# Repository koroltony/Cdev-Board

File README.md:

# C-DEV-Board

Documentation of CDEV board. PCB for breadboard-type development. USB/Battery powered

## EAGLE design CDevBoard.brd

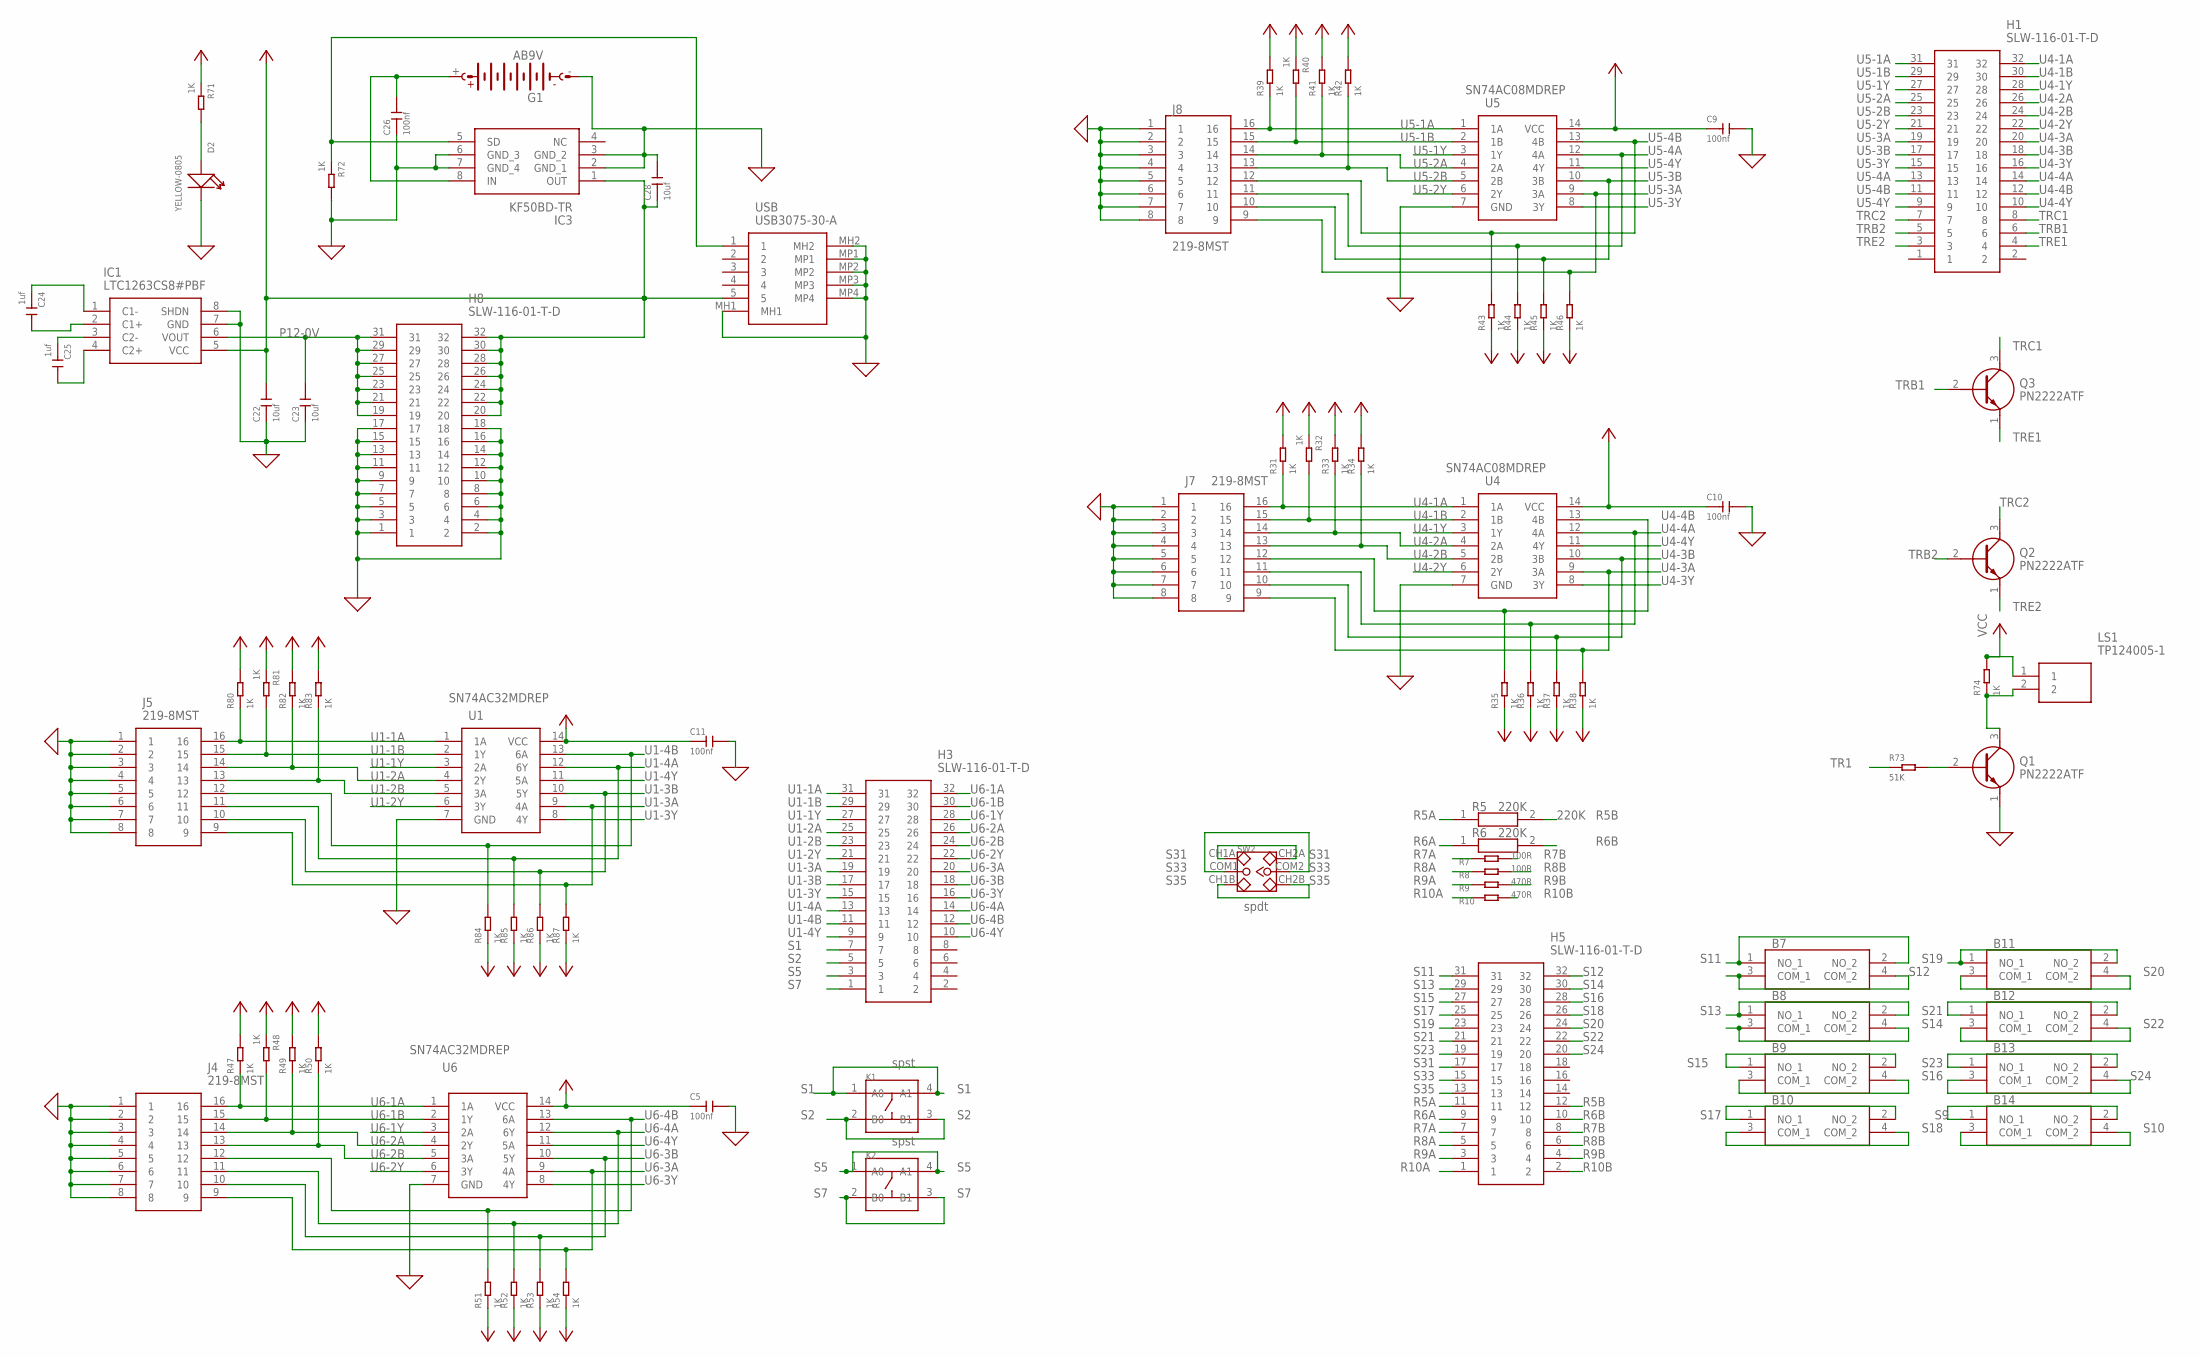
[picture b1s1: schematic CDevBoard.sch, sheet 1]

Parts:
B7, B8, B9, B10, B11, B12, B13, B14: 1301.9317; 13019317
C5, C9, C10, C11: 100nf; C0402
C22, C23, C28: 10uf; C0805
C24, C25: 1uf; C0805
C26: 100nf; C0603
D2: YELLOW-0805; LED-0805
G1: AB9V
H1, H3, H5, H8: SLW-116-01-T-D; SLW-116-01-X
IC1: LTC1263CS8#PBF; SOIC127P599X175-8N
IC3: KF50BD-TR; SOIC127P600X175-8N; MANUFACTURER_PART_NUMBER KF50BD-TR; MOUSER_PART_NUMBER 511-KF50BD-TR
J4, J5, J7, J8: 219-8MST; 2198MST
K1, K2: SMD-SWITCH-TACTILE-SPST-NO(4P-D6.0MM); SW4-SMD-6.0X6.0X5.0MM
LS1: TP124005-1; TP1240051
Q1, Q2, Q3: PN2222ATF; KA431AZTA
R5: 220K; RESAD1590W60L630D240
R6: 220K; RESAD1590W60L630D240; MANUFACTURER_PART_NUMBER CFR-25JR-52100R
R7, R8: 100R; PR-D2.3XL6.5MM
R9, R10: 470R; PR-D2.3XL6.5MM
R31, R32, R33, R34, R35, R36, R37, R38, R39, R40, R41, R42, R43, R44, R45, R46, R47, R48, R49, R50, R51, R52, R53, R54, R71, R72, R74, R80, R81, R82, R83, R84, R85, R86, R87: 1K; R0805
R73: 51K; R0603
SW2: DIP-TOGGLE-SWITCH-2CH-(2X3P-2.54); SW6-2.54-9.0X3.5X3.2+2.0MM
U1, U6: SN74AC04MDREP; SOIC127P600X175-14N; MANUFACTURER_PART_NUMBER SN74AC32MDREP
U4, U5: SN74AC08MDREP; SOIC127P600X175-14N
USB: USB3075-30-A; USB307530A

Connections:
0: C5.2, C9.2, C10.2, C11.2, C22.1, C23.1, C26.1, C28.2, D2.-, G1.-, H8.1, H8.2, H8.3, H8.4, H8.5, H8.6, H8.7, H8.8, H8.9, H8.10, H8.11, H8.12, H8.13, H8.14, H8.15, H8.16, H8.17, H8.18, IC1.7 (GND), IC1.8 (SHDN), IC3.2 (GND_1), IC3.3 (GND_2), IC3.6 (GND_3), IC3.7 (GND_4), J4.1, J4.2, J4.3, J4.4, J4.5, J4.6, J4.7, J4.8, J5.1, J5.2, J5.3, J5.4, J5.5, J5.6, J5.7, J5.8, J7.1, J7.2, J7.3, J7.4, J7.5, J7.6, J7.7, J7.8, J8.1, J8.2, J8.3, J8.4, J8.5, J8.6, J8.7, J8.8, Q1.1 (E), R72.2, U1.7 (GND), U4.7 (GND), U5.7 (GND), U6.7 (GND), USB.MH1, USB.MH2, USB.MP1, USB.MP2, USB.MP3, USB.MP4; also elsewhere on the board
unnamed: Q1.2 (B), R73.2
unnamed: LS1.2, Q1.3 (C), R74.1
unnamed: IC3.5 (SD), R72.1, USB.1
unnamed: C24.1, IC1.1 (C1-)
unnamed: C24.2, IC1.2 (C1+)
unnamed: C25.1, IC1.3 (C2-)
unnamed: C25.2, IC1.4 (C2+)
unnamed: C26.2, G1.+, IC3.8 (IN)
unnamed: D2.+, R71.2
P12-0V: C23.2, H8.19, H8.21, H8.23, H8.25, H8.27, H8.29, H8.31, IC1.6 (VOUT)
R5A: H5.11, R5.1
R5B: H5.12, R5.2
R6A: H5.9, R6.1
R6B: H5.10, R6.2
R7A: H5.7, R7.1
R7B: H5.8, R7.2
R8A: H5.5, R8.1
R8B: H5.6, R8.2
R9A: H5.3, R9.1
R9B: H5.4, R9.2
R10A: H5.1, R10.1
R10B: H5.2, R10.2
S1: H3.7, K1.1 (A0), K1.4 (A1)
S2: H3.5, K1.2 (B0), K1.3 (B1)
S5: H3.3, K2.1 (A0), K2.4 (A1)
S7: H3.1, K2.2 (B0), K2.3 (B1)
S9: B14.1 (NO_1), B14.2 (NO_2); also elsewhere on the board
S10: B14.3 (COM_1), B14.4 (COM_2); also elsewhere on the board
S11: B7.1 (NO_1), B7.2 (NO_2), H5.31
S12: B7.3 (COM_1), B7.4 (COM_2), H5.32
S13: B8.1 (NO_1), B8.2 (NO_2), H5.29
S14: B8.3 (COM_1), B8.4 (COM_2), H5.30
S15: B9.1 (NO_1), B9.2 (NO_2), H5.27
S16: B9.3 (COM_1), B9.4 (COM_2), H5.28
S17: B10.1 (NO_1), B10.2 (NO_2), H5.25
S18: B10.3 (COM_1), B10.4 (COM_2), H5.26
S19: B11.1 (NO_1), B11.2 (NO_2), H5.23
S20: B11.3 (COM_1), B11.4 (COM_2), H5.24
S21: B12.1 (NO_1), B12.2 (NO_2), H5.21
S22: B12.3 (COM_1), B12.4 (COM_2), H5.22
S23: B13.1 (NO_1), B13.2 (NO_2), H5.19
S24: B13.3 (COM_1), B13.4 (COM_2), H5.20
S31: H5.17, SW2.CH1A, SW2.CH2A
S33: H5.15, SW2.COM1, SW2.COM2
S35: H5.13, SW2.CH1B, SW2.CH2B
TR1: R73.1; also elsewhere on the board
TRB1: H1.6, Q3.2 (B)
TRB2: H1.5, Q2.2 (B)
TRC1: H1.8, Q3.3 (C)
TRC2: H1.7, Q2.3 (C)
TRE1: H1.4, Q3.1 (E)
TRE2: H1.3, Q2.1 (E)
U1-1A: H3.31, J5.16, R80.1, U1.1 (1A)
U1-1B: H3.29, J5.15, R81.2, U1.2 (1Y)
U1-1Y: H3.27, U1.3 (2A)
U1-2A: H3.25, J5.14, R82.1, U1.4 (2Y)
U1-2B: H3.23, J5.13, R83.1, U1.5 (3A)
U1-2Y: H3.21, U1.6 (3Y)
U1-3A: H3.19, J5.9, R87.2, U1.9 (4A)
U1-3B: H3.17, J5.10, R86.2, U1.10 (5Y)
U1-3Y: H3.15, U1.8 (4Y)
U1-4A: H3.13, J5.11, R85.2, U1.12 (6Y)
U1-4B: H3.11, J5.12, R84.2, U1.13 (6A)
U1-4Y: H3.9, U1.11 (5A)
U4-1A: H1.32, J7.16, R31.1, U4.1 (1A)
U4-1B: H1.30, J7.15, R32.2, U4.2 (1B)
U4-1Y: H1.28, U4.3 (1Y)
U4-2A: H1.26, J7.14, R33.1, U4.4 (2A)
U4-2B: H1.24, J7.13, R34.1, U4.5 (2B)
U4-2Y: H1.22, U4.6 (2Y)
U4-3A: H1.20, J7.9, R38.2, U4.9 (3A)
U4-3B: H1.18, J7.10, R37.2, U4.10 (3B)
U4-3Y: H1.16, U4.8 (3Y)
U4-4A: H1.14, J7.11, R36.2, U4.12 (4A)
U4-4B: H1.12, J7.12, R35.2, U4.13 (4B)
U4-4Y: H1.10, U4.11 (4Y)
U5-1A: H1.31, J8.16, R39.1, U5.1 (1A)
U5-1B: H1.29, J8.15, R40.2, U5.2 (1B)
U5-1Y: H1.27, U5.3 (1Y)
U5-2A: H1.25, J8.14, R41.1, U5.4 (2A)
U5-2B: H1.23, J8.13, R42.1, U5.5 (2B)
U5-2Y: H1.21, U5.6 (2Y)
U5-3A: H1.19, J8.9, R46.2, U5.9 (3A)
U5-3B: H1.17, J8.10, R45.2, U5.10 (3B)
U5-3Y: H1.15, U5.8 (3Y)
U5-4A: H1.13, J8.11, R44.2, U5.12 (4A)
U5-4B: H1.11, J8.12, R43.2, U5.13 (4B)
U5-4Y: H1.9, U5.11 (4Y)
U6-1A: H3.32, J4.16, R47.1, U6.1 (1A)
U6-1B: H3.30, J4.15, R48.2, U6.2 (1Y)
U6-1Y: H3.28, U6.3 (2A)
U6-2A: H3.26, J4.14, R49.1, U6.4 (2Y)
U6-2B: H3.24, J4.13, R50.1, U6.5 (3A)
U6-2Y: H3.22, U6.6 (3Y)
U6-3A: H3.20, J4.9, R54.2, U6.9 (4A)
U6-3B: H3.18, J4.10, R53.2, U6.10 (5Y)
U6-3Y: H3.16, U6.8 (4Y)
U6-4A: H3.14, J4.11, R52.2, U6.12 (6Y)
U6-4B: H3.12, J4.12, R51.2, U6.13 (6A)
U6-4Y: H3.10, U6.11 (5A)
VCC: C5.1, C9.1, C10.1, C11.1, C22.2, C28.1, H8.20, H8.22, H8.24, H8.26, H8.28, H8.30, H8.32, IC1.5 (VCC), IC3.1 (OUT), LS1.1, R31.2, R32.1, R33.2, R34.2, R35.1, R36.1, R37.1, R38.1, R39.2, R40.1, R41.2, R42.2, R43.1, R44.1, R45.1, R46.1, R47.2, R48.1, R49.2, R50.2, R51.1, R52.1, R53.1, R54.1, R71.1, R74.2, R80.2, R81.1, R82.2, R83.2, R84.1, R85.1, R86.1, R87.1, U1.14 (VCC), U4.14 (VCC), U5.14 (VCC), U6.14 (VCC), USB.5; also elsewhere on the board

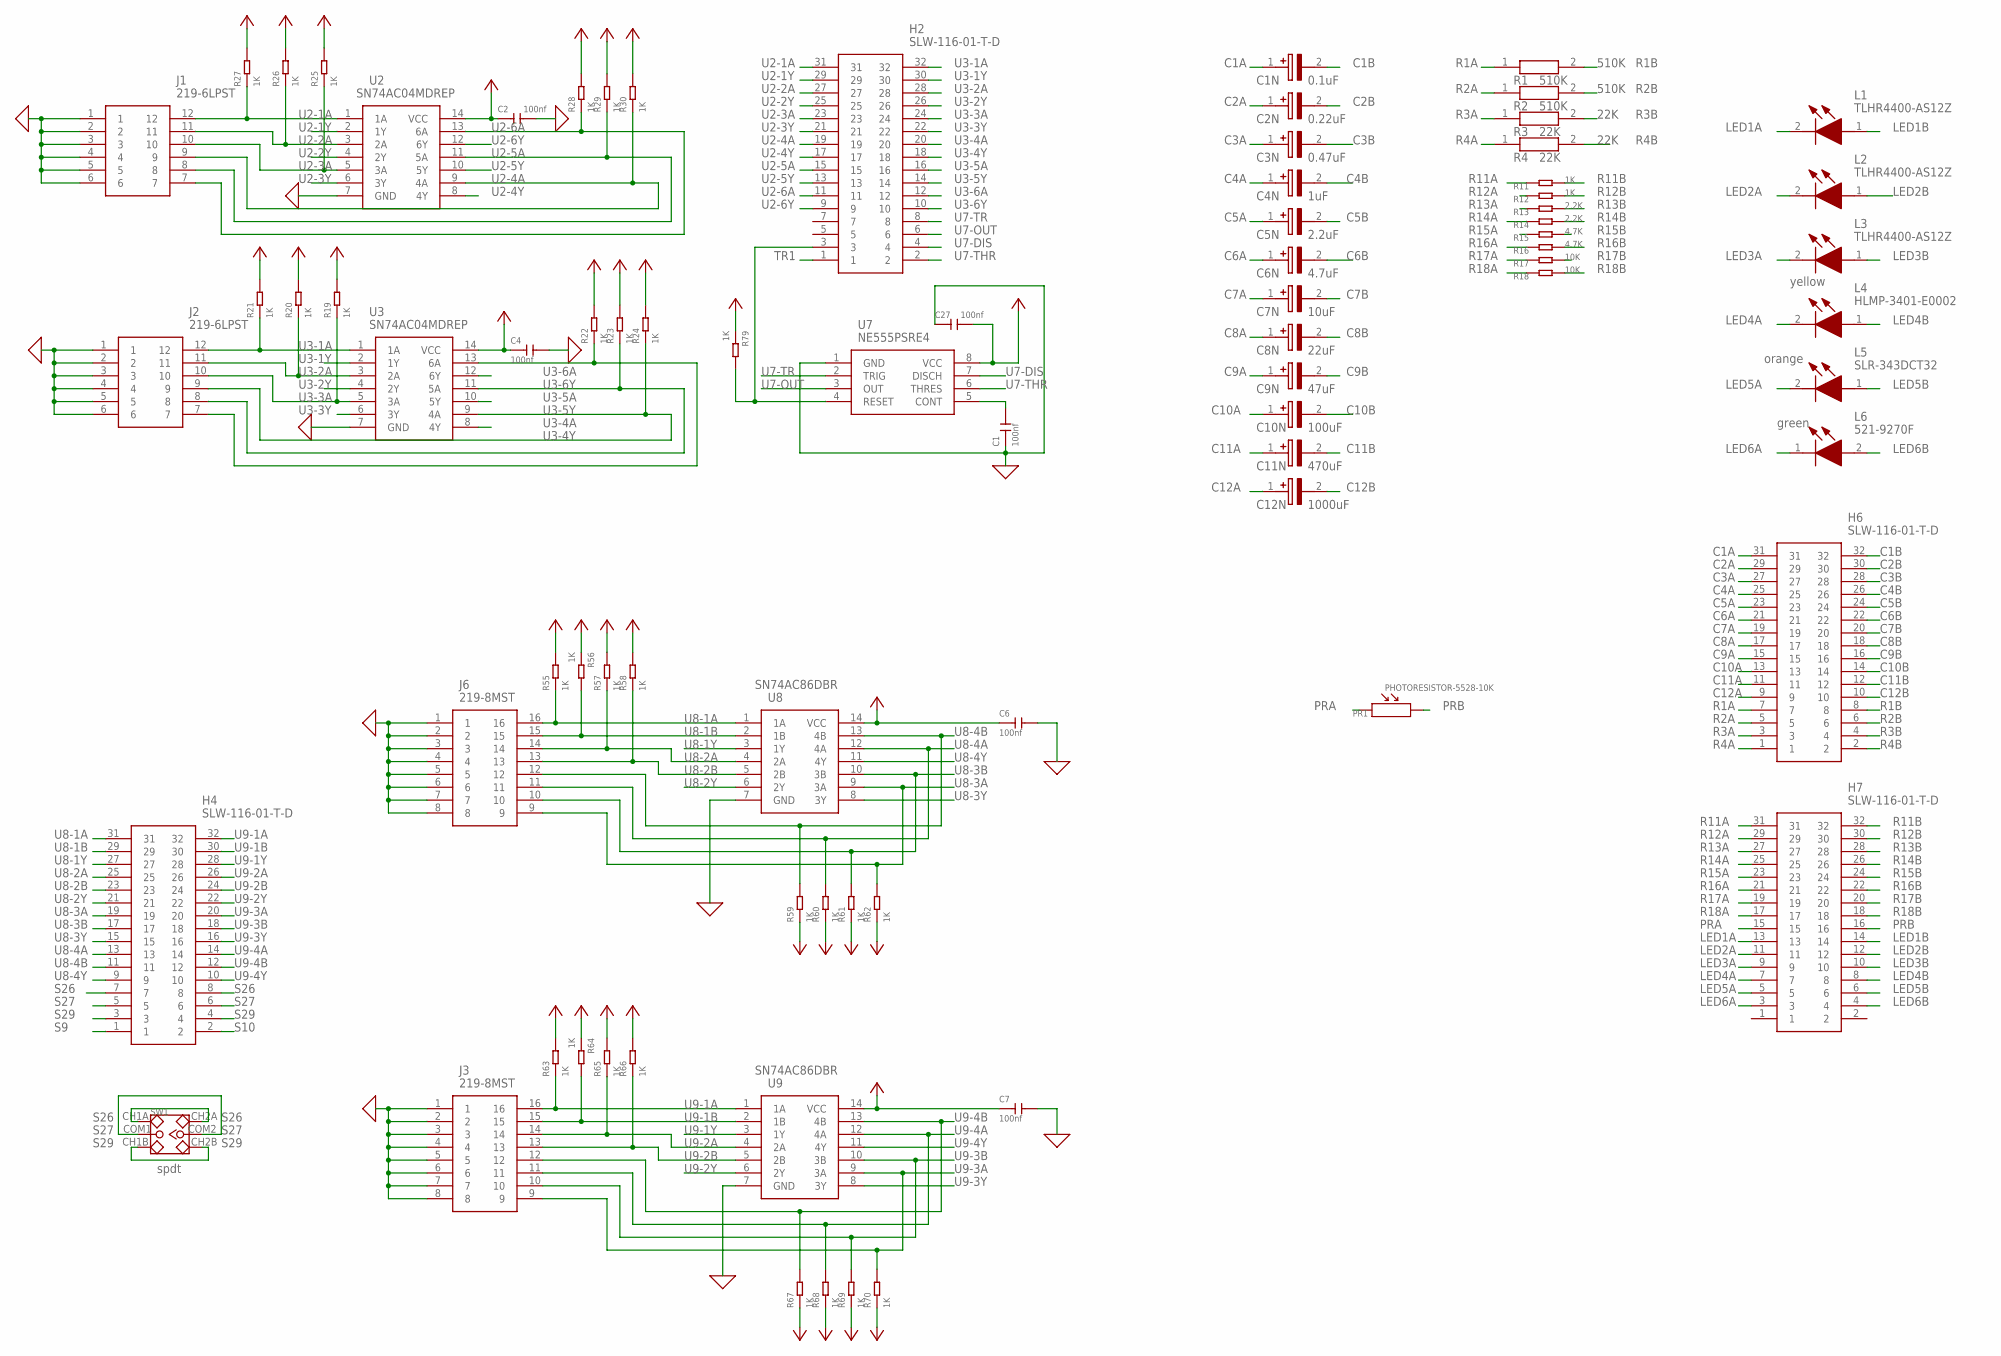
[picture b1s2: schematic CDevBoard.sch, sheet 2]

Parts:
C1, C2, C4, C6, C7, C27: 100nf; C0402
C1N: 0.1uF; CAPPRD200W52D500H1250
C2N: 0.22uF; CAPPRD200W52D500H1250
C3N: 0.47uF; CAPPRD200W52D500H1250
C4N: 1uF; CAPPRD200W52D500H1250
C5N: 2.2uF; CAPPRD200W52D500H1250
C6N: 4.7uF; CAPPRD200W52D500H1250
C7N: 10uF; CAPPRD200W50D500H1250
C8N: 22uF; CAPPRD200W52D500H1250
C9N: 47uF; CAPPRD200W52D500H1250
C10N: 100uF; CAPPRD200W52D500H1250
C11N: 470uF; CAPPRD200W52D500H1250
C12N: 1000uF; CAPPRD200W52D500H1250
H2, H4, H6, H7: SLW-116-01-T-D; SLW-116-01-X
J1, J2: 219-6LPST; 2196LPST
J3, J6: 219-8MST; 2198MST
L1, L2, L3: TLHR4400-AS12Z; TLHR4400AS12Z
L4: HLMP-3401-E0002; HLMP3401E0002
L5: SLR-343DCT32; SLR343DCT32
L6: 521-9270F; 5219270F
PR1: PHOTORESISTOR-5528-10K; SNR2-3.0
R1, R2: 510K; RESAD1590W60L630D240
R3, R4: 22K; RESAD1590W60L630D240
R11, R12: 1K; PR-D2.3XL6.5MM
R13, R14: 2.2K; PR-D2.3XL6.5MM
R15, R16: 4.7K; PR-D2.3XL6.5MM
R17, R18: 10K; PR-D2.3XL6.5MM
R19, R20, R21, R22, R23, R24, R25, R26, R27, R28, R29, R30, R55, R56, R57, R58, R59, R60, R61, R62, R63, R64, R65, R66, R67, R68, R69, R70, R79: 1K; R0805
SW1: DIP-TOGGLE-SWITCH-2CH-(2X3P-2.54); SW6-2.54-9.0X3.5X3.2+2.0MM
U2, U3: SN74AC04MDREP; SOIC127P600X175-14N
U7: NE555PSRE4; SOIC127P780X200-8N
U8, U9: SN74AC86DBR; SOP65P780X200-14N

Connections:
0: C1.1, C2.2, C4.2, C6.2, C7.2, C27.1, J1.1, J1.2, J1.3, J1.4, J1.5, J1.6, J2.1, J2.2, J2.3, J2.4, J2.5, J2.6, J3.1, J3.2, J3.3, J3.4, J3.5, J3.6, J3.7, J3.8, J6.1, J6.2, J6.3, J6.4, J6.5, J6.6, J6.7, J6.8, U2.7 (GND), U3.7 (GND), U7.1 (GND), U8.7 (GND), U9.7 (GND); also elsewhere on the board
C1A: C1N.1 (+), H6.31
C1B: C1N.2 (-), H6.32
C2A: C2N.1 (+), H6.29
C2B: C2N.2 (-), H6.30
C3A: C3N.1 (+), H6.27
C3B: C3N.2 (-), H6.28
C4A: C4N.1 (+), H6.25
C4B: C4N.2 (-), H6.26
C5A: C5N.1 (+), H6.23
C5B: C5N.2 (-), H6.24
C6A: C6N.1 (+), H6.21
C6B: C6N.2 (-), H6.22
C7A: C7N.1 (+), H6.19
C7B: C7N.2 (-), H6.20
C8A: C8N.1 (+), H6.17
C8B: C8N.2 (-), H6.18
C9A: C9N.1 (+), H6.15
C9B: C9N.2 (-), H6.16
C10A: C10N.1 (+), H6.13
C10B: C10N.2 (-), H6.14
C11A: C11N.1 (+), H6.11
C11B: C11N.2 (-), H6.12
C12A: C12N.1 (+), H6.9
C12B: C12N.2 (-), H6.10
LED1A: H7.13, L1.2 (K)
LED1B: H7.14, L1.1 (A)
LED2A: H7.11, L2.2 (K)
LED2B: H7.12, L2.1 (A)
LED3A: H7.9, L3.2 (K)
LED3B: H7.10, L3.1 (A)
LED4A: H7.7, L4.2 (K)
LED4B: H7.8, L4.1 (A)
LED5A: H7.5, L5.2 (K)
LED5B: H7.6, L5.1 (A)
LED6A: H7.3, L6.1 (K)
LED6B: H7.4, L6.2 (A)
unnamed: C1.2, U7.5 (CONT)
unnamed: H2.3, R79.2, U7.4 (RESET)
PRA: H7.15, PR1.1
PRB: H7.16, PR1.2
R1A: H6.7, R1.1
R1B: H6.8, R1.2
R2A: H6.5, R2.1
R2B: H6.6, R2.2
R3A: H6.3, R3.1
R3B: H6.4, R3.2
R4A: H6.1, R4.1
R4B: H6.2, R4.2
R11A: H7.31, R11.1
R11B: H7.32, R11.2
R12A: H7.29, R12.1
R12B: H7.30, R12.2
R13A: H7.27, R13.1
R13B: H7.28, R13.2
R14A: H7.25, R14.1
R14B: H7.26, R14.2
R15A: H7.23, R15.1
R15B: H7.24, R15.2
R16A: H7.21, R16.1
R16B: H7.22, R16.2
R17A: H7.19, R17.1
R17B: H7.20, R17.2
R18A: H7.17, R18.1
R18B: H7.18, R18.2
S9: H4.1; also elsewhere on the board
S10: H4.2; also elsewhere on the board
S26: H4.7, H4.8, SW1.CH1A, SW1.CH2A
S27: H4.5, H4.6, SW1.COM1, SW1.COM2
S29: H4.3, H4.4, SW1.CH1B, SW1.CH2B
TR1: H2.1; also elsewhere on the board
U2-1A: H2.31, J1.12, R27.1, U2.1 (1A)
U2-1Y: H2.29, U2.2 (1Y)
U2-2A: H2.27, J1.11, R26.1, U2.3 (2A)
U2-2Y: H2.25, U2.4 (2Y)
U2-3A: H2.23, J1.10, R25.1, U2.5 (3A)
U2-3Y: H2.21, U2.6 (3Y)
U2-4A: H2.19, J1.9, R30.1, U2.9 (4A)
U2-4Y: H2.17, U2.8 (4Y)
U2-5A: H2.15, J1.8, R29.1, U2.11 (5A)
U2-5Y: H2.13, U2.10 (5Y)
U2-6A: H2.11, J1.7, R28.1, U2.13 (6A)
U2-6Y: H2.9, U2.12 (6Y)
U3-1A: H2.32, J2.12, R21.1, U3.1 (1A)
U3-1Y: H2.30, U3.2 (1Y)
U3-2A: H2.28, J2.11, R20.1, U3.3 (2A)
U3-2Y: H2.26, U3.4 (2Y)
U3-3A: H2.24, J2.10, R19.1, U3.5 (3A)
U3-3Y: H2.22, U3.6 (3Y)
U3-4A: H2.20, J2.9, R24.1, U3.9 (4A)
U3-4Y: H2.18, U3.8 (4Y)
U3-5A: H2.16, J2.8, R23.1, U3.11 (5A)
U3-5Y: H2.14, U3.10 (5Y)
U3-6A: H2.12, J2.7, R22.1, U3.13 (6A)
U3-6Y: H2.10, U3.12 (6Y)
U7-DIS: H2.4, U7.7 (DISCH)
U7-OUT: H2.6, U7.3 (OUT)
U7-THR: H2.2, U7.6 (THRES)
U7-TR: H2.8, U7.2 (TRIG)
U8-1A: H4.31, J6.16, R55.1, U8.1 (1A)
U8-1B: H4.29, J6.15, R56.2, U8.2 (1B)
U8-1Y: H4.27, U8.3 (1Y)
U8-2A: H4.25, J6.14, R57.1, U8.4 (2A)
U8-2B: H4.23, J6.13, R58.1, U8.5 (2B)
U8-2Y: H4.21, U8.6 (2Y)
U8-3A: H4.19, J6.9, R62.2, U8.9 (3A)
U8-3B: H4.17, J6.10, R61.2, U8.10 (3B)
U8-3Y: H4.15, U8.8 (3Y)
U8-4A: H4.13, J6.11, R60.2, U8.12 (4A)
U8-4B: H4.11, J6.12, R59.2, U8.13 (4B)
U8-4Y: H4.9, U8.11 (4Y)
U9-1A: H4.32, J3.16, R63.1, U9.1 (1A)
U9-1B: H4.30, J3.15, R64.2, U9.2 (1B)
U9-1Y: H4.28, U9.3 (1Y)
U9-2A: H4.26, J3.14, R65.1, U9.4 (2A)
U9-2B: H4.24, J3.13, R66.1, U9.5 (2B)
U9-2Y: H4.22, U9.6 (2Y)
U9-3A: H4.20, J3.9, R70.2, U9.9 (3A)
U9-3B: H4.18, J3.10, R69.2, U9.10 (3B)
U9-3Y: H4.16, U9.8 (3Y)
U9-4A: H4.14, J3.11, R68.2, U9.12 (4A)
U9-4B: H4.12, J3.12, R67.2, U9.13 (4B)
U9-4Y: H4.10, U9.11 (4Y)
VCC: C2.1, C4.1, C6.1, C7.1, C27.2, R19.2, R20.2, R21.2, R22.2, R23.2, R24.2, R25.2, R26.2, R27.2, R28.2, R29.2, R30.2, R55.2, R56.1, R57.2, R58.2, R59.1, R60.1, R61.1, R62.1, R63.2, R64.1, R65.2, R66.2, R67.1, R68.1, R69.1, R70.1, R79.1, U2.14 (VCC), U3.14 (VCC), U7.8 (VCC), U8.14 (VCC), U9.14 (VCC); also elsewhere on the board

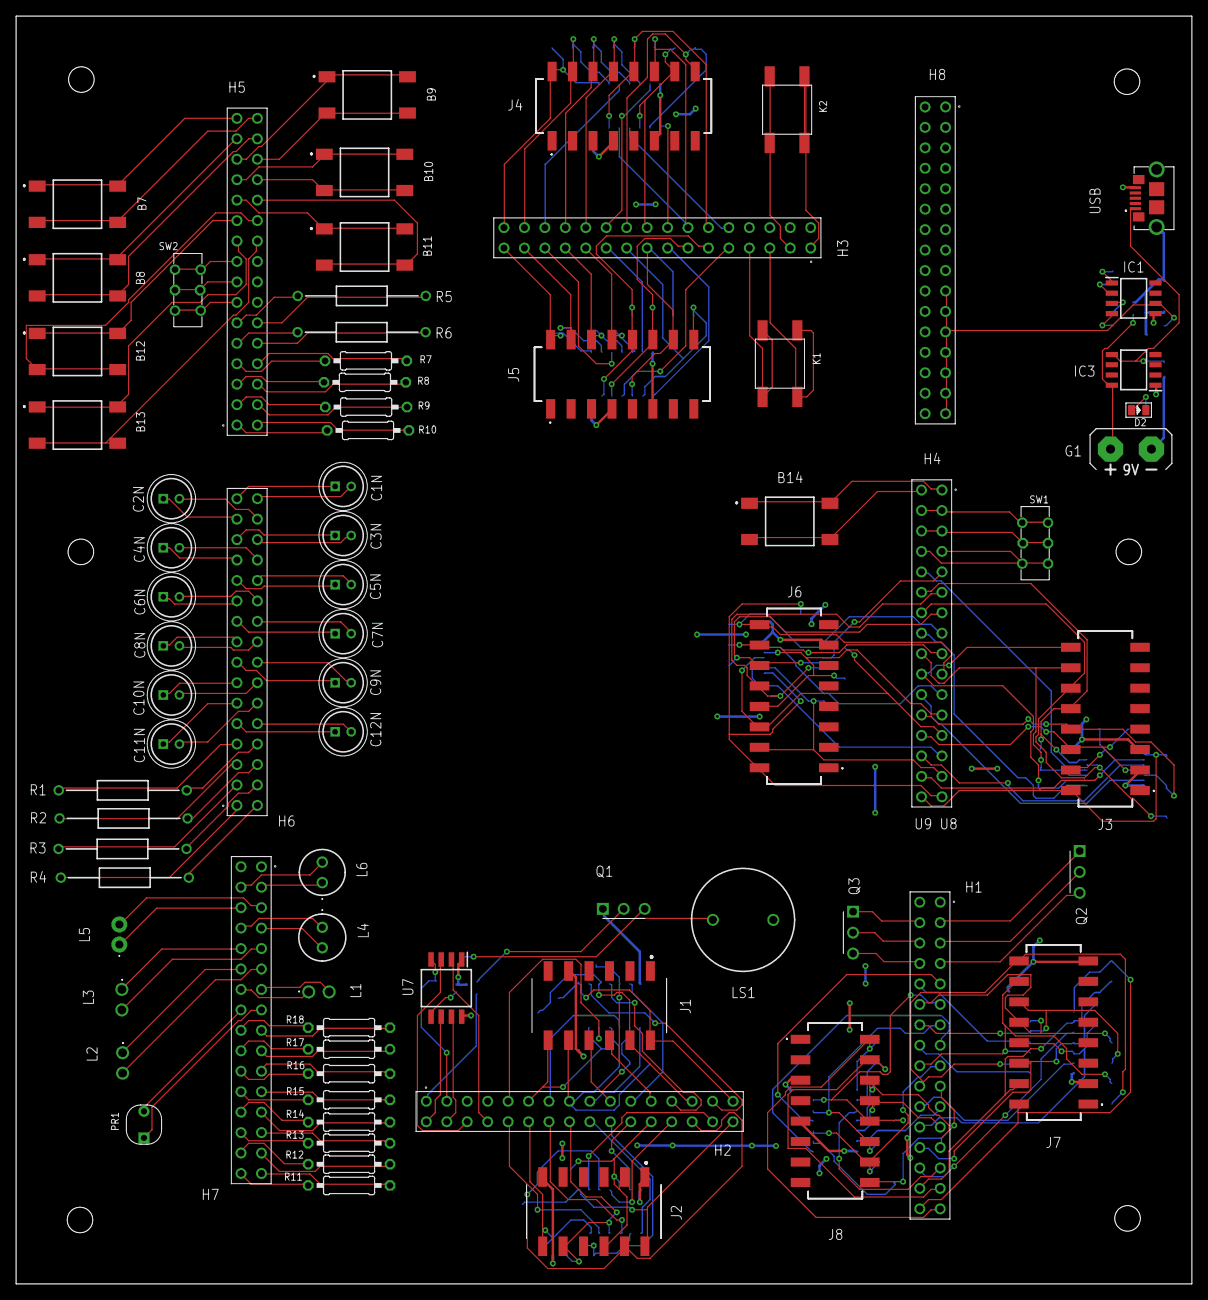
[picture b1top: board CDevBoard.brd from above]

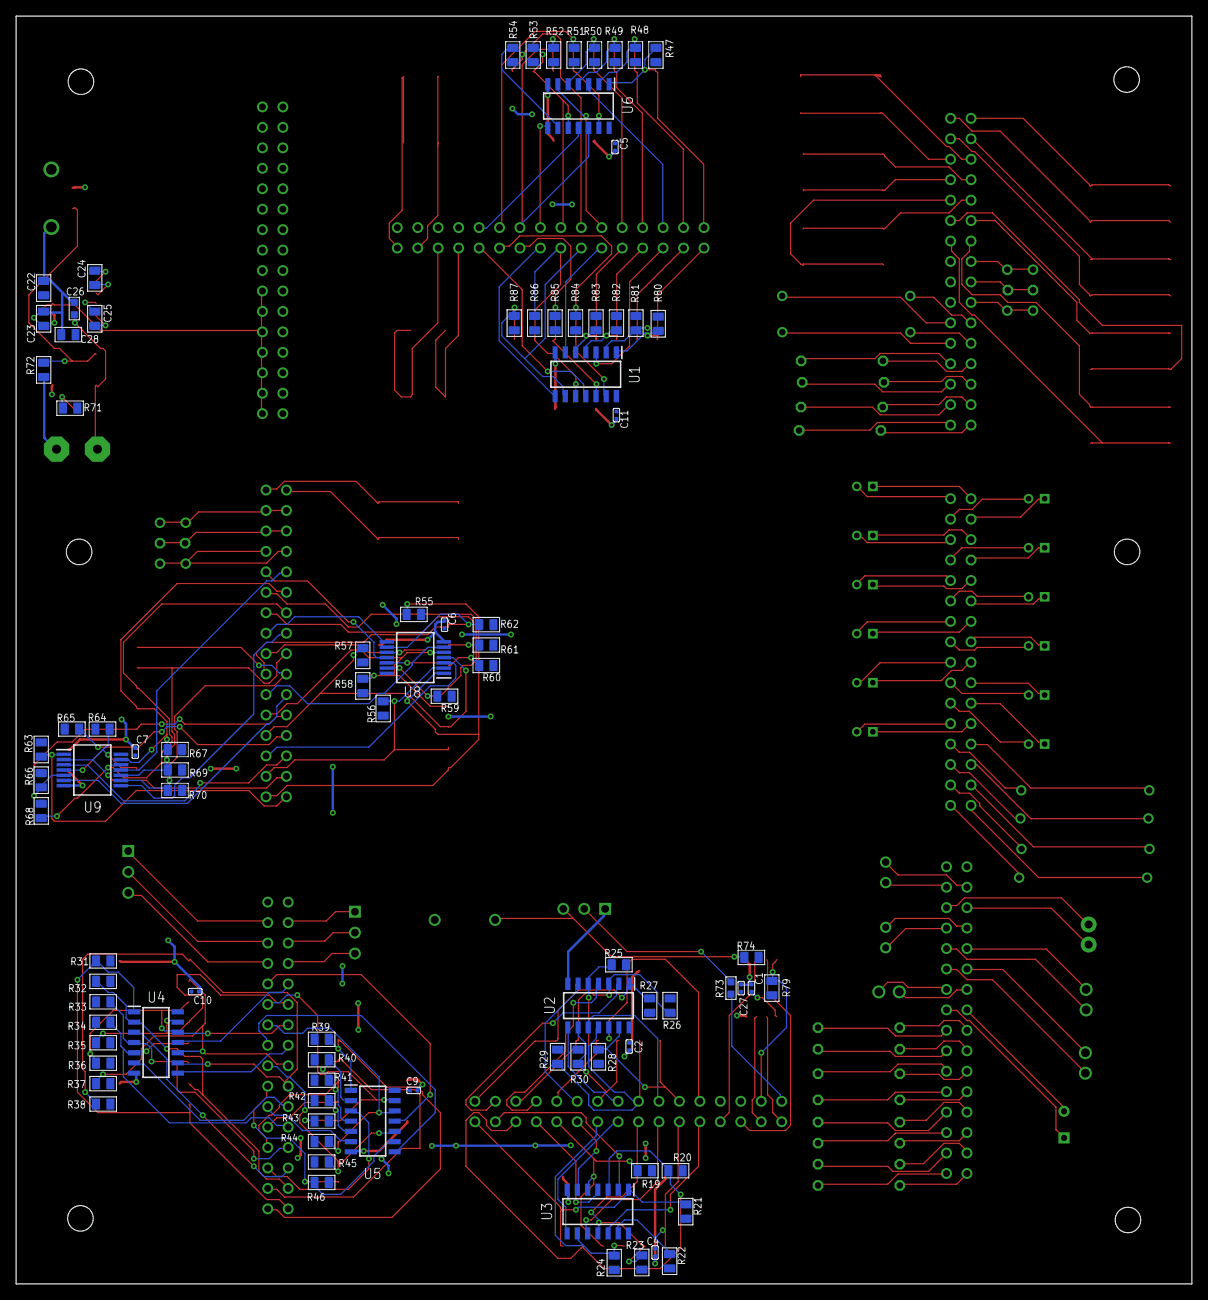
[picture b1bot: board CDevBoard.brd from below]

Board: 2 copper layers, 146.1 x 157.5 mm, 164 parts (89 on the bottom side), 221 nets.

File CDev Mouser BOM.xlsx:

Mfr Part Number (Input) | Manufacturer Part Number | Mouser Part Number | Manufacturer Name | Description | Quantity 1 | Unit Price 1 | Quantity 2 | Unit Price 2 | Quantity 3 | Unit Price 3 | Quantity 4 | Unit Price 4 | Quantity 5 | Unit Price 5 | Order Quantity | Order Unit Price | Min./Mult. | Availability | Lead Time in Days | Lifecycle | NCNR | RoHS | Pb Free | Package Type | Datasheet URL | Product Image | Design Risk
1301.9317000000001
302010024
860010272005
860010273011
860010274015
860010772001
302010178
302010179
302010138
860010672002
860010672004
860010672005
860020672006
860020672008
ESK106M010AC3AA
860010272001
860010272003
304090039
235
SLW-116-01-T-D
LTC1263CS8#PBF
KF50BD-TR
219-6LPST
219-8MST
311020004
TLHR4400-AS12Z
HLMP-3401-E0002
SLR-343DCT32
521-9270F
TP124005-1
314020017
PN2222 PBFREE
CFR-25JR-52-510K
301020000
301020010
301020012
301020001
301010311
CFR-25JR-52-22K
CFR-25JR-52-220K
301020017
301010311
301010226
301020029
311010004
SN74AC32MDREP
SN74AC04MDREP
SN74AC08MDREP
NE555PSRE4
SN74AC86DBR
USB3075-30-A

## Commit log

2022-09-10 Documentation of CDEV project
2022-09-10 Pictures of brd, sch, and gerber!
